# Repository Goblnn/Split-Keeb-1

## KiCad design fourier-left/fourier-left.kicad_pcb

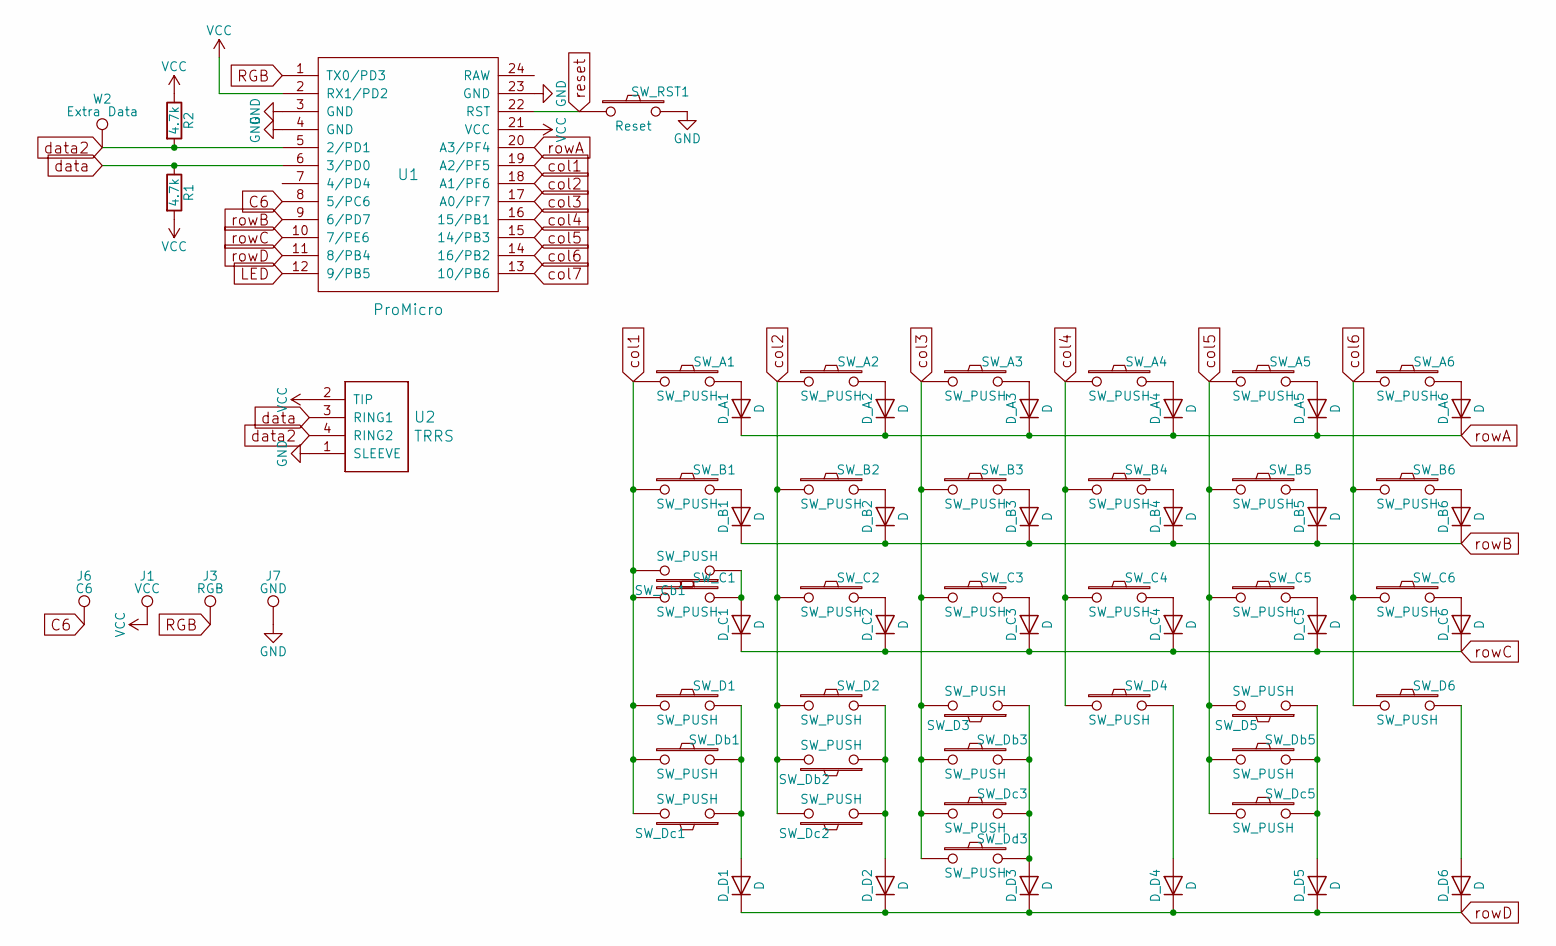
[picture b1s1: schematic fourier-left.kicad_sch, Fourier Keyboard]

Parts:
D_A1, D_A2, D_A3, D_A4, D_A5, D_A6: D; Diode-Hybrid-Back
D_B1, D_B2, D_B3, D_B4, D_B5, D_B6: D; Diode-Hybrid-Back
D_C1, D_C2, D_C3, D_C4, D_C5, D_C6: D; Diode-Hybrid-Back
D_D1, D_D2, D_D3, D_D4, D_D5, D_D6: D; Diode-Hybrid-Back
J1: VCC; Single-Pad
J3: RGB; Single-Pad
J6: C6; Single-Pad
J7: GND; Single-Pad
R1, R2: 4.7k; Resistor-Hybrid-Back
SW_A1, SW_A2, SW_A3, SW_A4, SW_A5, SW_A6: SW_PUSH; MX-1U-NoLED
SW_B1: SW_PUSH; MX-1.25U-NoLED
SW_B2, SW_B3, SW_B4, SW_B5, SW_B6: SW_PUSH; MX-1U-NoLED
SW_C1: SW_PUSH; MX-1.75U-NoLED
SW_C2, SW_C3, SW_C4, SW_C5, SW_C6: SW_PUSH; MX-1U-NoLED
SW_Cb1: SW_PUSH; MX-1.25U-NoLED
SW_D1, SW_D3: SW_PUSH; MX-1.25U-NoLED
SW_D2, SW_D4, SW_D6: SW_PUSH; MX-1U-NoLED
SW_D5: SW_PUSH; MX-2.75U-ReversedStabilizers-NoLED
SW_Db1, SW_Db2: SW_PUSH; MX-1.5U-NoLED
SW_Db3: SW_PUSH; MX-1.25U-NoLED
SW_Db5: SW_PUSH; MX-2.25U-ReversedStabilizers-NoLED
SW_Dc1, SW_Dc2: SW_PUSH; MX-1U-NoLED
SW_Dc3: SW_PUSH; MX-1.5U-NoLED
SW_Dc5: SW_PUSH; MX-1.25U-NoLED
SW_Dd3: SW_PUSH; MX-1U-NoLED
SW_RST1: Reset; SW_Tactile_SPST_Angled_MJTP1117
U1: ProMicro; ArduinoProMicro-ZigZag
U2: TRRS; TRRS-PJ-320A
W2: Extra Data; Single-Pad

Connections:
C6: J6.1, U1.8 (5/PC6)
GND: J7.1, SW_RST1.2, U1.3 (GND), U1.4 (GND), U1.23 (GND), U2.1 (SLEEVE)
LED: U1.12 (9/PB5)
unnamed: D_A1.2 (A), SW_A1.2
unnamed: D_A2.2 (A), SW_A2.2
unnamed: D_A3.2 (A), SW_A3.2
unnamed: D_A4.2 (A), SW_A4.2
unnamed: D_A5.2 (A), SW_A5.2
unnamed: D_A6.2 (A), SW_A6.2
unnamed: D_B1.2 (A), SW_B1.2
unnamed: D_B2.2 (A), SW_B2.2
unnamed: D_B3.2 (A), SW_B3.2
unnamed: D_B4.2 (A), SW_B4.2
unnamed: D_B5.2 (A), SW_B5.2
unnamed: D_B6.2 (A), SW_B6.2
unnamed: D_C1.2 (A), SW_C1.2, SW_Cb1.1
unnamed: D_C2.2 (A), SW_C2.2
unnamed: D_C3.2 (A), SW_C3.2
unnamed: D_C4.2 (A), SW_C4.2
unnamed: D_C5.2 (A), SW_C5.2
unnamed: D_C6.2 (A), SW_C6.2
unnamed: D_D1.2 (A), SW_D1.2, SW_Db1.2, SW_Dc1.1
unnamed: D_D2.2 (A), SW_D2.2, SW_Db2.1, SW_Dc2.1
unnamed: D_D3.2 (A), SW_D3.1, SW_Db3.2, SW_Dc3.2, SW_Dd3.2
unnamed: D_D4.2 (A), SW_D4.2
unnamed: D_D5.2 (A), SW_D5.1, SW_Db5.2, SW_Dc5.2
unnamed: D_D6.2 (A), SW_D6.2
RGB: J3.1, U1.1 (TX0/PD3)
VCC: J1.1, R1.2, R2.1, U1.2 (RX1/PD2), U1.21 (VCC), U2.2 (TIP)
col1: SW_A1.1, SW_B1.1, SW_C1.1, SW_Cb1.2, SW_D1.1, SW_Db1.1, SW_Dc1.2, U1.19 (A2/PF5)
col2: SW_A2.1, SW_B2.1, SW_C2.1, SW_D2.1, SW_Db2.2, SW_Dc2.2, U1.18 (A1/PF6)
col3: SW_A3.1, SW_B3.1, SW_C3.1, SW_D3.2, SW_Db3.1, SW_Dc3.1, SW_Dd3.1, U1.17 (A0/PF7)
col4: SW_A4.1, SW_B4.1, SW_C4.1, SW_D4.1, U1.16 (15/PB1)
col5: SW_A5.1, SW_B5.1, SW_C5.1, SW_D5.2, SW_Db5.1, SW_Dc5.1, U1.15 (14/PB3)
col6: SW_A6.1, SW_B6.1, SW_C6.1, SW_D6.1, U1.14 (16/PB2)
col7: U1.13 (10/PB6)
data: R1.1, U1.6 (3/PD0), U2.3 (RING1)
data2: R2.2, U1.5 (2/PD1), U2.4 (RING2), W2.1
reset: SW_RST1.1, U1.22 (RST)
rowA: D_A1.1 (K), D_A2.1 (K), D_A3.1 (K), D_A4.1 (K), D_A5.1 (K), D_A6.1 (K), U1.20 (A3/PF4)
rowB: D_B1.1 (K), D_B2.1 (K), D_B3.1 (K), D_B4.1 (K), D_B5.1 (K), D_B6.1 (K), U1.9 (6/PD7)
rowC: D_C1.1 (K), D_C2.1 (K), D_C3.1 (K), D_C4.1 (K), D_C5.1 (K), D_C6.1 (K), U1.10 (7/PE6)
rowD: D_D1.1 (K), D_D2.1 (K), D_D3.1 (K), D_D4.1 (K), D_D5.1 (K), D_D6.1 (K), U1.11 (8/PB4)

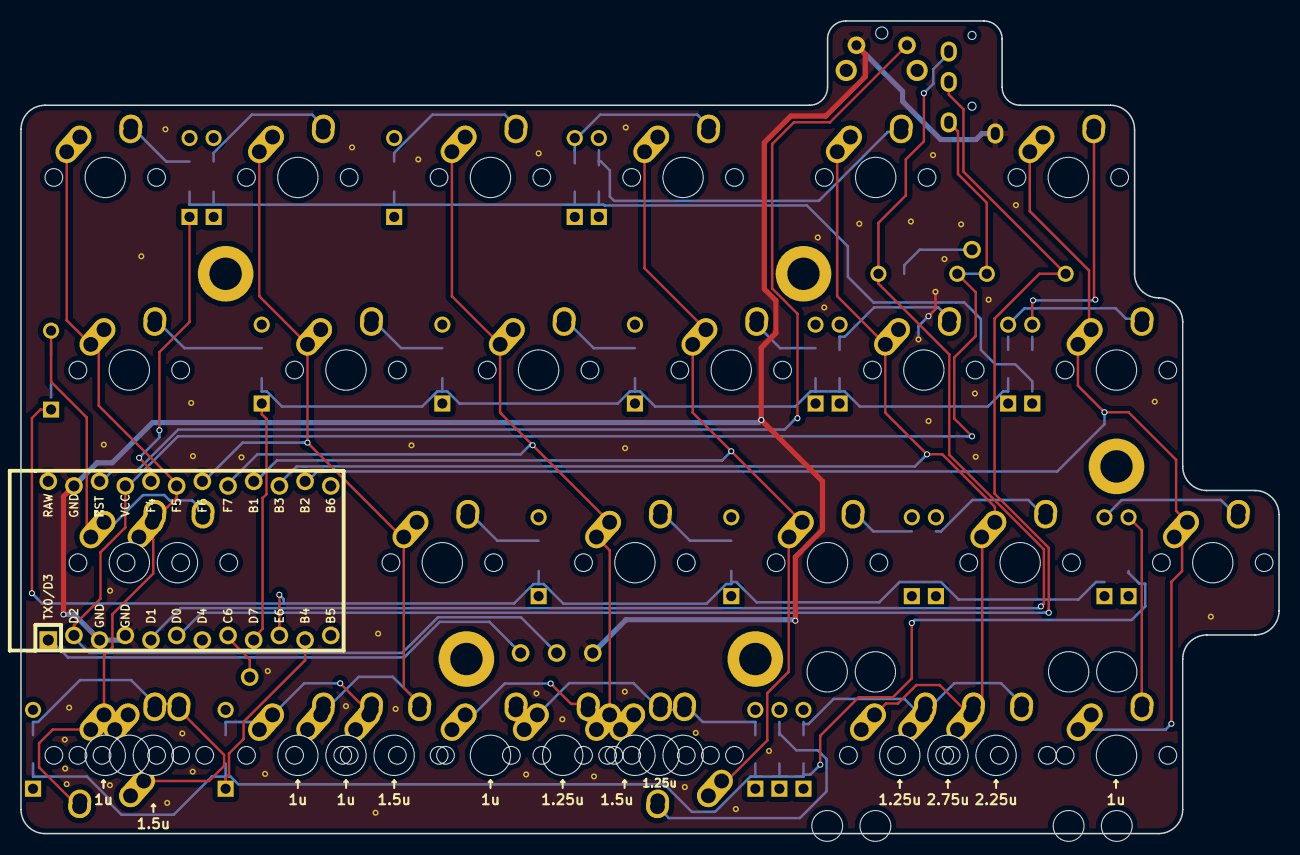
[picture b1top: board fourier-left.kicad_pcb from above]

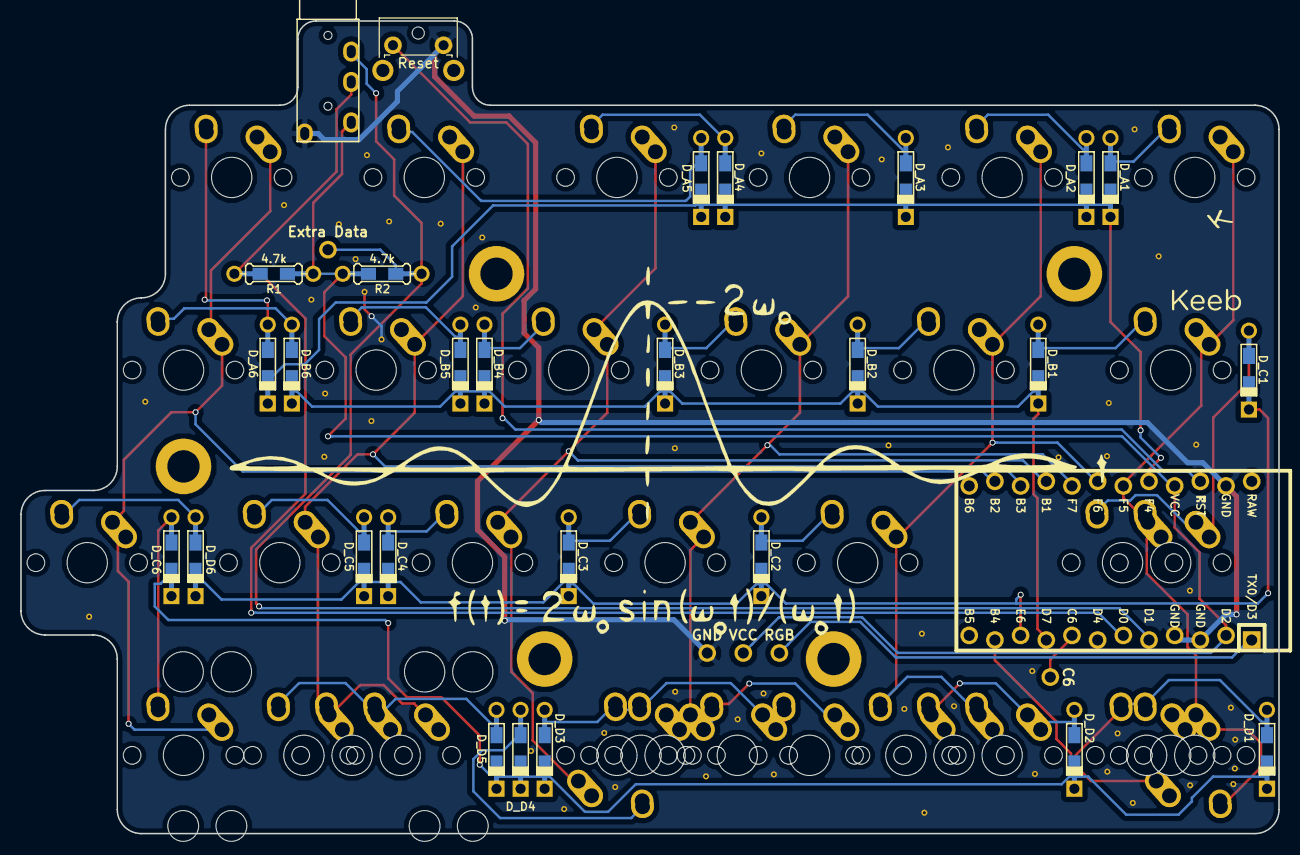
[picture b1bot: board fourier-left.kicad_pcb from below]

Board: 2 copper layers, 124.4 x 80.4 mm, 68 parts (7 on the bottom side), 41 nets.

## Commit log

2025-05-31 adad
